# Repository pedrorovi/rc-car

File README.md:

# RC Car Project

This repository contains all the necessary files and resources to design, configure, and develop an RC car. The project is organized into three main folders:

## Folder Structure

### 1. `kicad/` - Hardware Design

This folder contains the hardware design files for the RC car, created using KiCad. It includes:

- PCB layout files (`.kicad_pcb`)
- Schematic files (`.kicad_sch`)
- Gerber files for manufacturing
- Drill files and reports

### 2. `stm32-cube-ide/` - STM32L432KC Configuration

This folder contains the configuration files for the STM32L432KC microcontroller, set up using STM32CubeIDE. It includes:

- Peripheral initialization
- Clock configuration
- Pin assignments

### 3. `platformio/` - Firmware Development

This folder contains the firmware source code for the RC car, developed using PlatformIO. It includes:

- Source code for motor control, sensors, and communication
- Configuration files for PlatformIO
- Unit tests for firmware components

## Getting Started

### Prerequisites

- [KiCad](https://kicad.org/) for hardware design
- [STM32CubeIDE](https://www.st.com/en/development-tools/stm32cubeide.html) for microcontroller configuration
- [PlatformIO](https://platformio.org/) for firmware development

### Steps to Build the RC Car

1. **Hardware Design**: Open the `kicad/` folder in KiCad to view and modify the PCB and schematic designs. Generate Gerber files for manufacturing.
2. **Microcontroller Configuration**: Open the `stm32-cube-ide/` folder in STM32CubeIDE to configure the STM32L432KC microcontroller.
3. **Firmware Development**: Use PlatformIO to write and upload firmware to the microcontroller. Navigate to the `platformio/` folder and run:

   ```sh
   make build_embedded

## Shopping list

### Nucleo

[STM32L432KC](https://www.digikey.es/es/products/detail/stmicroelectronics/NUCLEO-L432KC/6132763)

### Radio

[Goolsky Flysky FS-GT5 2.4G 6CH Transmitter Remote Controller with FS-BS6 Receiver for RC Car Crawler Boat](https://a.co/d/gxiTpZ9)

### Car

[AXSPEED-Kit](https://es.aliexpress.com/item/1005004083219971.html?spm=a2g0o.order_list.order_list_main.313.2c05194ddy0I9h&gatewayAdapt=glo2esp)

### Motor

[Rocket-Motor](https://es.aliexpress.com/item/1005003152797506.html?spm=a2g0o.order_list.order_list_main.278.2c05194ddy0I9h&gatewayAdapt=glo2esp)

### Servo

[INJORA-Servo Digital](https://es.aliexpress.com/item/1005005066982557.html?spm=a2g0o.order_list.order_list_main.273.2c05194ddy0I9h&gatewayAdapt=glo2esp)

### Batteries

[Zeee 2S Lipo Batería 50C 2200mAh 7.4V Batería Corta con Enchufe XT60](https://amzn.eu/d/79buMsG)

[Motor Battery](https://es.aliexpress.com/item/1005004770752418.html?spm=a2g0o.order_list.order_list_main.223.2c05194ddy0I9h&gatewayAdapt=glo2esp)

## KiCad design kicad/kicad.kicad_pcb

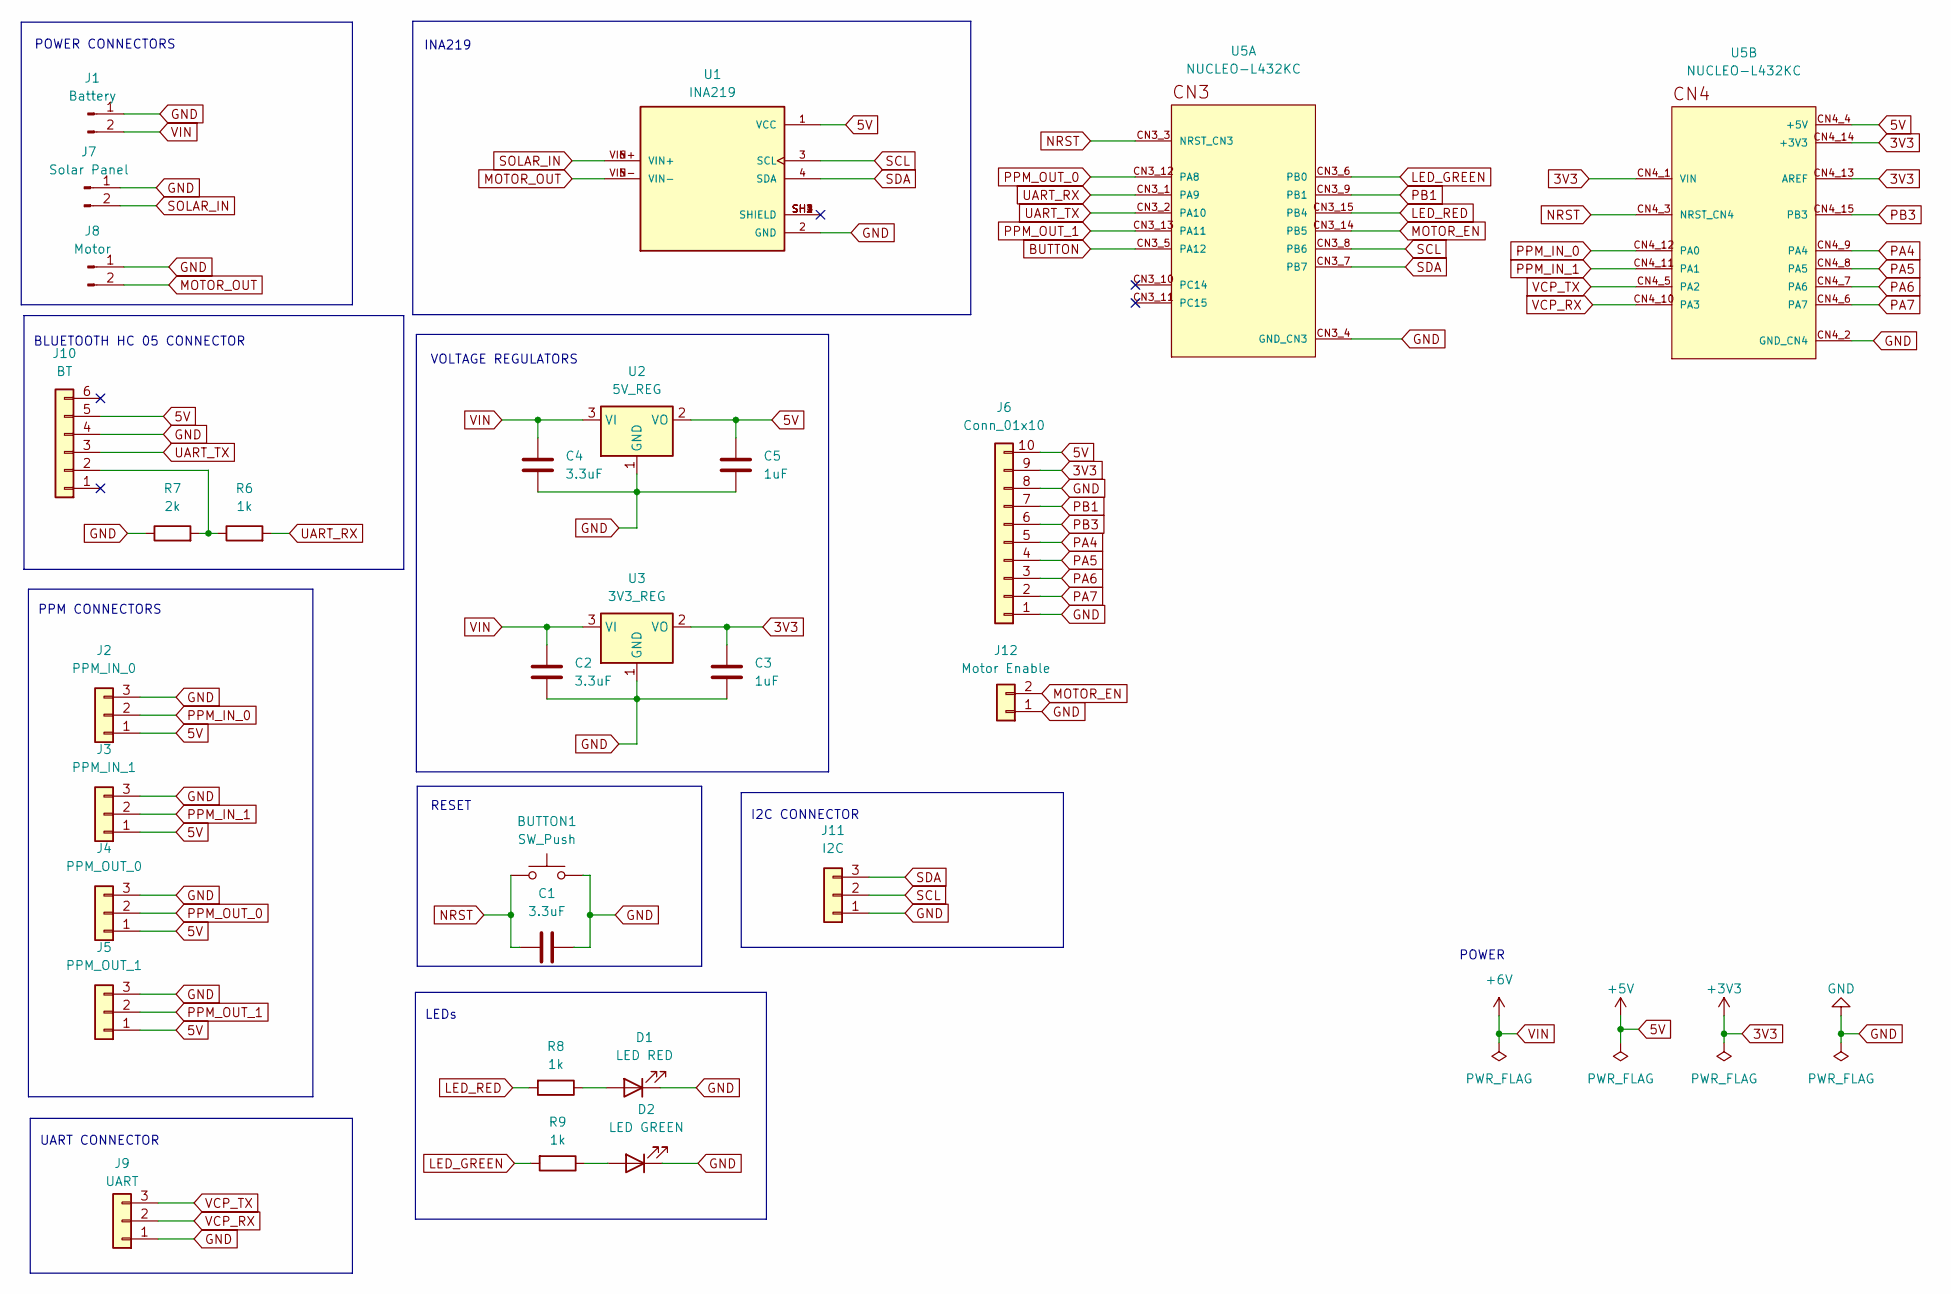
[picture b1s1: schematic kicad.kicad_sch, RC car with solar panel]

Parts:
BUTTON1: SW_Push; SW_SPST_PTS645
C1, C2, C4: 3.3uF; C_0805_2012Metric
C3, C5: 1uF; C_0805_2012Metric
D1: LED RED; LED_2010_5025Metric
D2: LED GREEN; LED_2010_5025Metric
J1: Battery; AMASS_XT60-F_1x02_P7.20mm_Vertical
J2: PPM_IN_0; PinHeader_1x03_P2.54mm_Vertical
J3: PPM_IN_1; PinHeader_1x03_P2.54mm_Vertical
J4: PPM_OUT_0; PinHeader_1x03_P2.54mm_Vertical
J5: PPM_OUT_1; PinHeader_1x03_P2.54mm_Vertical
J6: Conn_01x10; PinSocket_1x10_P2.54mm_Vertical
J7: Solar Panel; AMASS_XT60-F_1x02_P7.20mm_Vertical
J8: Motor; AMASS_XT60-F_1x02_P7.20mm_Vertical
J9: UART; PinHeader_1x03_P2.54mm_Vertical
J10: BT; PinSocket_1x06_P2.54mm_Vertical
J11: I2C; PinHeader_1x03_P2.54mm_Vertical
J12: Motor Enable; PinSocket_1x02_P2.54mm_Vertical
R6, R8, R9: 1k; R_0805_2012Metric
R7: 2k; R_0805_2012Metric
U1: INA219; MODULE_904; PARTREV C
U2: 5V_REG; SOT-223-3_TabPin2
U3: 3V3_REG; SOT-223-3_TabPin2
U5: NUCLEO-L432KC; MODULE_NUCLEO-L432KC; PARTREV N/A

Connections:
3V3: C3.1, J6.9, U3.2 (VO), U5.CN4_1 (VIN), U5.CN4_13 (AREF), U5.CN4_14 (+3V3)
5V: C5.1, J2.1, J3.1, J4.1, J5.1, J6.10, J10.5, U1.1 (VCC), U2.2 (VO), U5.CN4_4 (+5V)
BUTTON: U5.CN3_5 (PA12)
GND: BUTTON1.2, C1.1, C2.2, C3.2, C4.2, C5.2, D1.1 (K), D2.1 (K), J1.1, J2.3, J3.3, J4.3, J5.3, J6.1, J6.8, J7.1, J8.1, J9.1, J10.4, J11.1, J12.1, R7.1, U1.2 (GND), U2.1 (GND), U3.1 (GND), U5.CN3_4 (GND_CN3), U5.CN4_2 (GND_CN4)
LED_GREEN: R9.2, U5.CN3_6 (PB0)
LED_RED: R8.2, U5.CN3_15 (PB4)
MOTOR_EN: J12.2, U5.CN3_14 (PB5)
MOTOR_OUT: J8.2, U1.5 (VIN-), U1.VIN-
NRST: BUTTON1.1, C1.2, U5.CN3_3 (NRST_CN3), U5.CN4_3 (NRST_CN4)
unnamed: D1.2 (A), R8.1
unnamed: D2.2 (A), R9.1
unnamed: J10.2, R6.1, R7.2
PA4: J6.5, U5.CN4_9 (PA4)
PA5: J6.4, U5.CN4_8 (PA5)
PA6: J6.3, U5.CN4_7 (PA6)
PA7: J6.2, U5.CN4_6 (PA7)
PB1: J6.7, U5.CN3_9 (PB1)
PB3: J6.6, U5.CN4_15 (PB3)
PPM_IN_0: J2.2, U5.CN4_12 (PA0)
PPM_IN_1: J3.2, U5.CN4_11 (PA1)
PPM_OUT_0: J4.2, U5.CN3_12 (PA8)
PPM_OUT_1: J5.2, U5.CN3_13 (PA11)
SCL: J11.2, U1.3 (SCL), U5.CN3_8 (PB6)
SDA: J11.3, U1.4 (SDA), U5.CN3_7 (PB7)
SOLAR_IN: J7.2, U1.6 (VIN+), U1.VIN+
UART_RX: R6.2, U5.CN3_1 (PA9)
UART_TX: J10.3, U5.CN3_2 (PA10)
VCP_RX: J9.2, U5.CN4_10 (PA3)
VCP_TX: J9.3, U5.CN4_5 (PA2)
VIN: C2.1, C4.1, J1.2, U2.3 (VI), U3.3 (VI)

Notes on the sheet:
BLUETOOTH HC 05 CONNECTOR
POWER
PPM CONNECTORS
VOLTAGE REGULATORS
INA219
LEDs
UART CONNECTOR
I2C CONNECTOR
RESET
POWER CONNECTORS

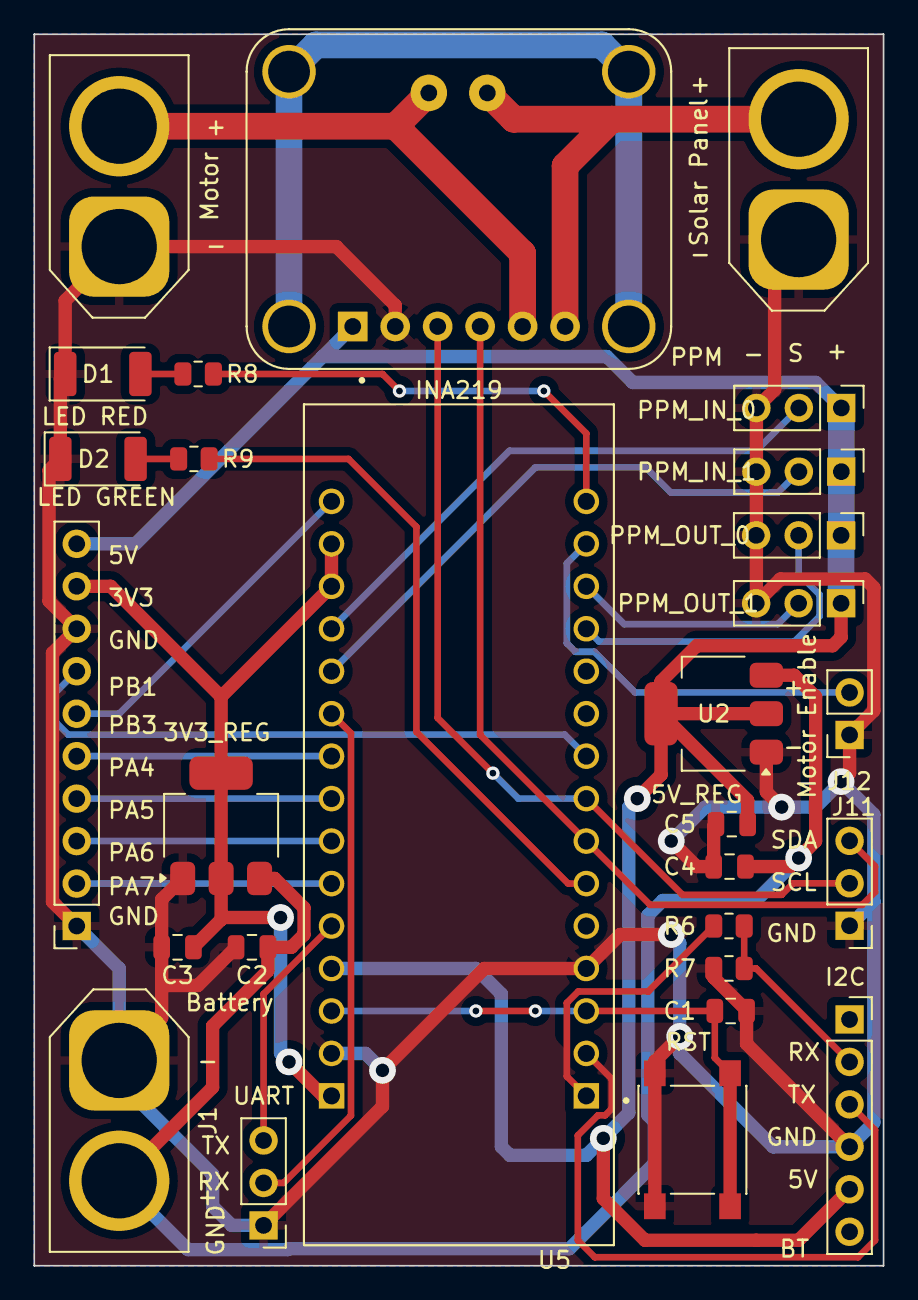
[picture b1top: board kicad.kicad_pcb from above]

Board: 2 copper layers, 50.8 x 73.7 mm, 28 parts (0 on the bottom side), 29 nets.

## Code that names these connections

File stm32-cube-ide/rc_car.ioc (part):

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Mcu.Name=STM32L432K(B-C)Ux
Mcu.Package=UFQFPN32
Mcu.UserName=STM32L432KCUx
PA0.GPIOParameters=GPIO_Label
PA0.GPIO_Label=PPM_IN_0
PA0.Signal=S_TIM2_CH1
PA1.GPIOParameters=GPIO_Label
PA1.GPIO_Label=PPM_IN_1
PA1.Signal=S_TIM2_CH2
PA10.GPIOParameters=GPIO_Label
PA10.GPIO_Label=BT_RX
PA10.Mode=Asynchronous
PA10.Signal=USART1_RX
PA11.GPIOParameters=GPIO_Label
PA11.GPIO_Label=PPM_OUT_1
PA11.Signal=S_TIM1_CH4
PA2.GPIOParameters=GPIO_Label
PA2.GPIO_Label=DEBUG_TX
PA2.Mode=Asynchronous
PA2.Signal=USART2_TX
PA3.GPIOParameters=GPIO_Label
PA3.GPIO_Label=DEBUG_RX
PA3.Mode=Asynchronous
PA3.Signal=USART2_RX
PA8.GPIOParameters=GPIO_Label
PA8.GPIO_Label=PPM_OUT_0
PA8.Signal=S_TIM1_CH1
PA9.GPIOParameters=GPIO_Label
PA9.GPIO_Label=BT_TX
PA9.Mode=Asynchronous
PA9.Signal=USART1_TX
PB0.GPIOParameters=GPIO_Label
PB0.GPIO_Label=LED_RED
PB0.Signal=GPIO_Output
PB4\ (NJTRST).GPIOParameters=GPIO_Label
PB4\ (NJTRST).GPIO_Label=LED_GREEN
PB4\ (NJTRST).Signal=GPIO_Output
PB5.GPIOParameters=GPIO_Label
PB5.GPIO_Label=MOTOR_EN
PB5.Signal=GPIO_Output
PB6.GPIOParameters=GPIO_Label
PB6.GPIO_Label=SCL
PB6.Mode=I2C
PB6.Signal=I2C1_SCL
PB7.GPIOParameters=GPIO_Label
PB7.GPIO_Label=SDA
PB7.Mode=I2C
PB7.Signal=I2C1_SDA
RCC.HSE_VALUE=8000000
RCC.SYSCLKFreq_VALUE=32000000
RCC.SYSCLKSource=RCC_SYSCLKSOURCE_PLLCLK
board=NUCLEO-L432KC
boardIOC=true

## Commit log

2025-04-13 add cube ide folder
2025-04-13 added kicad
2025-04-13 added pio
2025-04-13 added gallery images
2025-04-13 renamed
2025-04-13 update shopping list with links to car model and motor battery
2025-04-13 update README with additional shopping list items
2025-04-13 update README to remove repository cloning instructions
2025-04-13 add PCB image to README and include it in the gallery
